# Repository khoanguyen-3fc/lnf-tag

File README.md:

# LnF Tag

OpenHaystack-based Lost and Found Tag

<table>
<tr>
<td colspan="2"></td>
</tr>
<tr>
<td></td>
<td></td>
</tr>
</table>

## BOM

| Reference | Quantity | Description                           |
| --------- | -------- | ------------------------------------- |
| U1        | 1        | E104-BT5005A module                   |
| C1, C2    | 2        | C0603 10pF                            |
| Y1        | 1        | 3215 32.768Mhz Crystal                |
| PCB       | 1        | Custom PCB                            |
| Battery   | 2        | CR2032/CR2025/CR2016 with solder tabs |

## Battery life estimation

With the help of the XTAL, the power consumption is around 6.27uA.

| Battery type | Typical Capacity | Estimated life |
| ------------ | ---------------- | -------------- |
| 2xCR2032     | 2x220mAh         | ~8 years       |
| 2xCR2025     | 2x150mAh         | ~5.4 years     |
| 2xCR2016     | 2x75mAh          | ~2.7 years     |

## Credits

- [OpenHaystack](https://github.com/seemoo-lab/openhaystack)
- [Ultra low power alternative firmware](https://github.com/acalatrava/openhaystack-firmware)

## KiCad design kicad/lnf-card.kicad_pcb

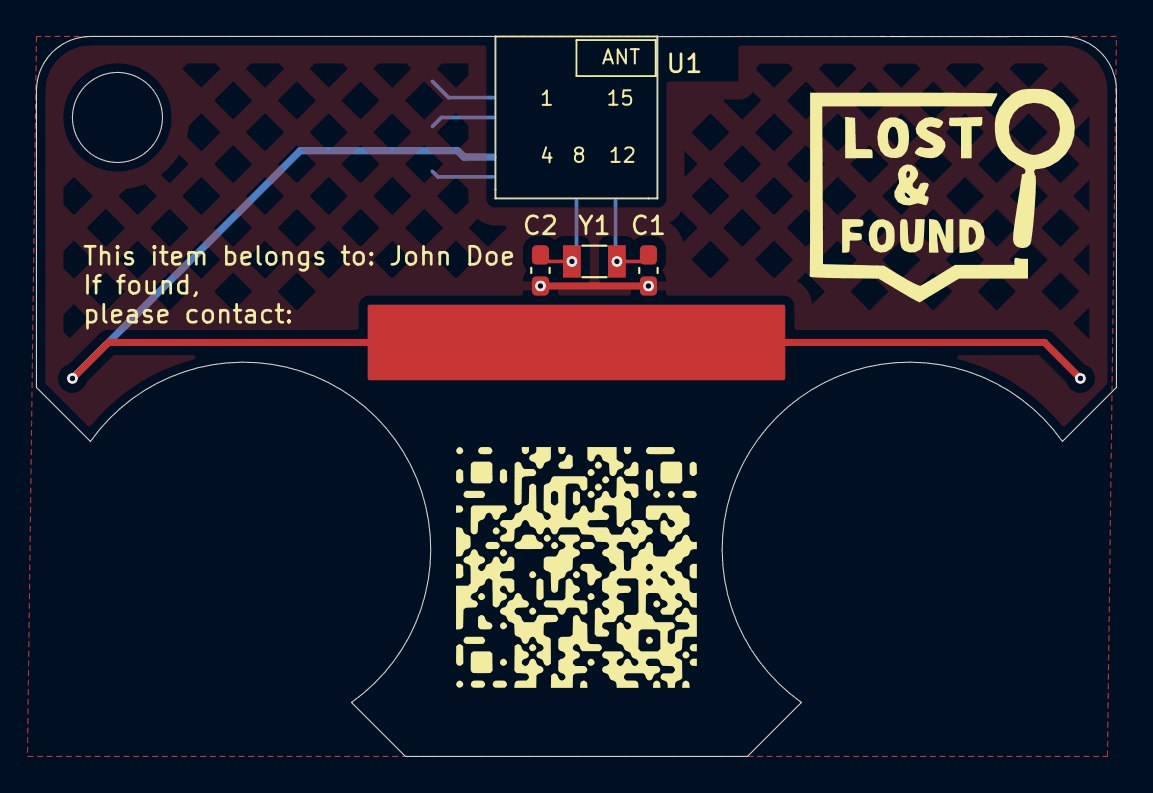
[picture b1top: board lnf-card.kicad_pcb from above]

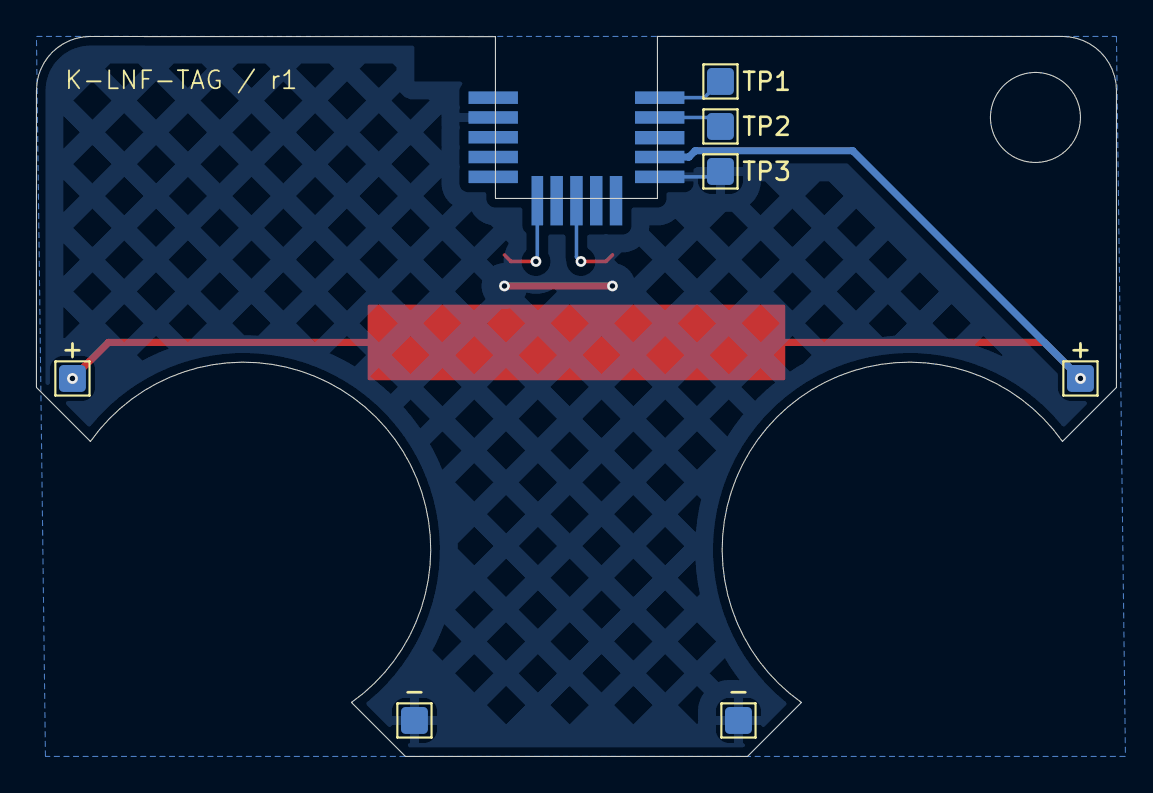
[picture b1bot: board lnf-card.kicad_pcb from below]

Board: 2 copper layers, 60.0 x 40.0 mm, 11 parts (7 on the bottom side), 6 nets.

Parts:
+: TestPoint; TestPoint_Pad_1.5x1.5mm
+#2: TestPoint; TestPoint_Pad_1.5x1.5mm
-: TestPoint; TestPoint_Pad_1.5x1.5mm
-#2: TestPoint; TestPoint_Pad_1.5x1.5mm
C1, C2: C; C_0603_1608Metric_Pad1.08x0.95mm_HandSolder
TP1, TP2, TP3: TestPoint; TestPoint_Pad_1.5x1.5mm
U1: BT5005A; E104-BT5005A_1
Y1: Crystal; Crystal_SMD_3215-2Pin_3.2x1.5mm

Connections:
+BATT: +.1, +#2.1, U1.4 (VDD)
GND: -.1, -#2.1, C1.2, C2.2, TP3.1, U1.5 (VSS), U1.14 (VSS)
unnamed: C2.1, U1.8 (XL1/P0.00), Y1.2
unnamed: C1.1, U1.10 (XL2/P0.01), Y1.1
SWCLK: TP1.1, U1.1 (SWDCLK)
SWDIO: TP2.1, U1.2 (SWDIO)

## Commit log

2026-03-04 :zap: Add KiCad project files
2026-03-06 :pencil: Update README.md
